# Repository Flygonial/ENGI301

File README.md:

<h1>ENGI301</h1>
Repository for ENGI301 course work

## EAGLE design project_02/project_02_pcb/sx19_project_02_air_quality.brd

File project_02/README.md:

This is the implementation for assignment project_02 in the course ENGI 301 at Rice University.

Included are the schematics, layout, and library in Autodesk EAGLE, along with basic manufacturing (gerber) files, a BOM, screenshots and PDFs that additionall document the design.

The board exists with the express purpose to implement the circuit in project_01 that joined all the PocketBeagle, PMS5003, CCS811, AHT10, and ILI9341 LCD together to form a more
elegant air quality module. Further work may entail design of a relatively rudimentary 3D printed case that utilizes the mounting holes on the PCB design, and this would likely still
run off USB power for packaging concerns.

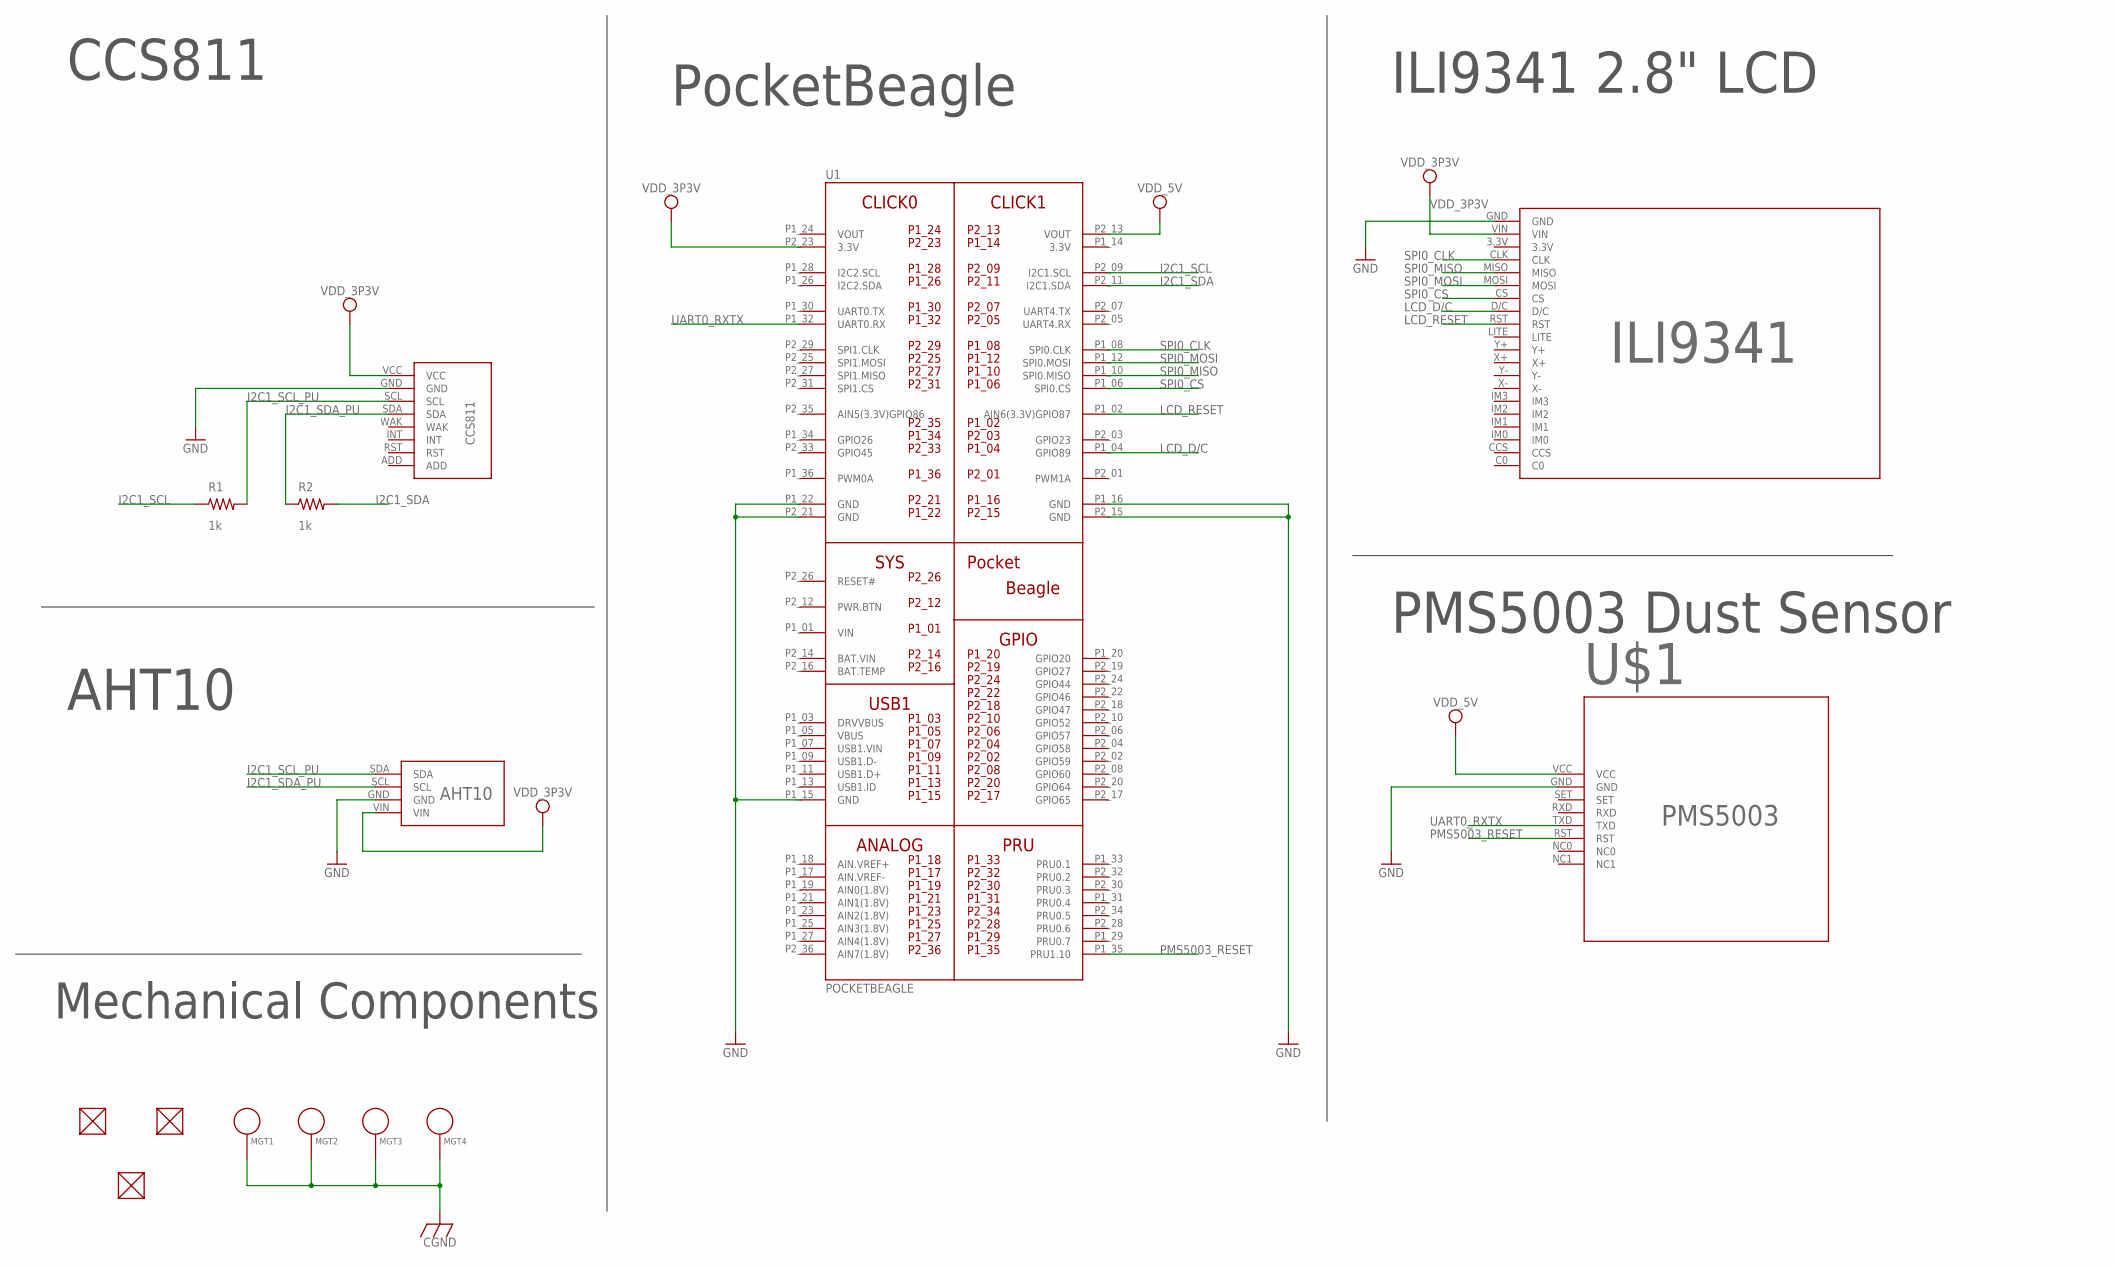
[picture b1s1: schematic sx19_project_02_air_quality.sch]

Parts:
B1: AHT10
B2: CCS811
B3: ILI9341
FUD1, FUD2, FUD3: FIDUCIAL; FIDUCIAL_40MIL
MGT1, MGT2, MGT3, MGT4: MOUNTING_HOLE
R1, R2: 1k; R0603
U1: POCKETBEAGLE
U$1: PMS5003

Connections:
3.3V: U1.P1_14 (3.3V)
BAT.VIN: U1.P2_14 (BAT.VIN)
CGND: MGT1.P$1, MGT2.P$1, MGT3.P$1, MGT4.P$1
GND: B1.GND, B2.GND, B3.GND, U1.P1_15 (GND), U1.P1_16 (GND), U1.P1_22 (GND), U1.P2_15 (GND), U1.P2_21 (GND), U$1.GND
I2C1_SCL: R1.1, U1.P2_09 (I2C1.SCL)
I2C1_SCL_PU: B1.SDA, B2.SCL, R1.2
I2C1_SDA: R2.2, U1.P2_11 (I2C1.SDA)
I2C1_SDA_PU: B1.SCL, B2.SDA, R2.1
LCD_D/C: B3.D/C, U1.P1_04 (GPIO89)
LCD_RESET: B3.RST, U1.P1_02 (AIN6(3.3V)GPIO87)
PMS5003_RESET: U1.P1_35 (PRU1.10), U$1.RST
SPI0_CLK: B3.CLK, U1.P1_08 (SPI0.CLK)
SPI0_CS: B3.CS, U1.P1_06 (SPI0.CS)
SPI0_MISO: B3.MISO, U1.P1_10 (SPI0.MISO)
SPI0_MOSI: B3.MOSI, U1.P1_12 (SPI0.MOSI)
UART0_RXTX: U1.P1_32 (UART0.RX), U$1.TXD
VDD_3P3V: B1.VIN, B2.VCC, B3.VIN, U1.P2_23 (3.3V)
VDD_5V: U1.P2_13 (VOUT), U$1.VCC
VIN: U1.P1_01 (VIN)
VOUT: U1.P1_24 (VOUT)

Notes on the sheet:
PocketBeagle
CCS811
AHT10
ILI9341 2.8" LCD
PMS5003 Dust Sensor
Mechanical Components

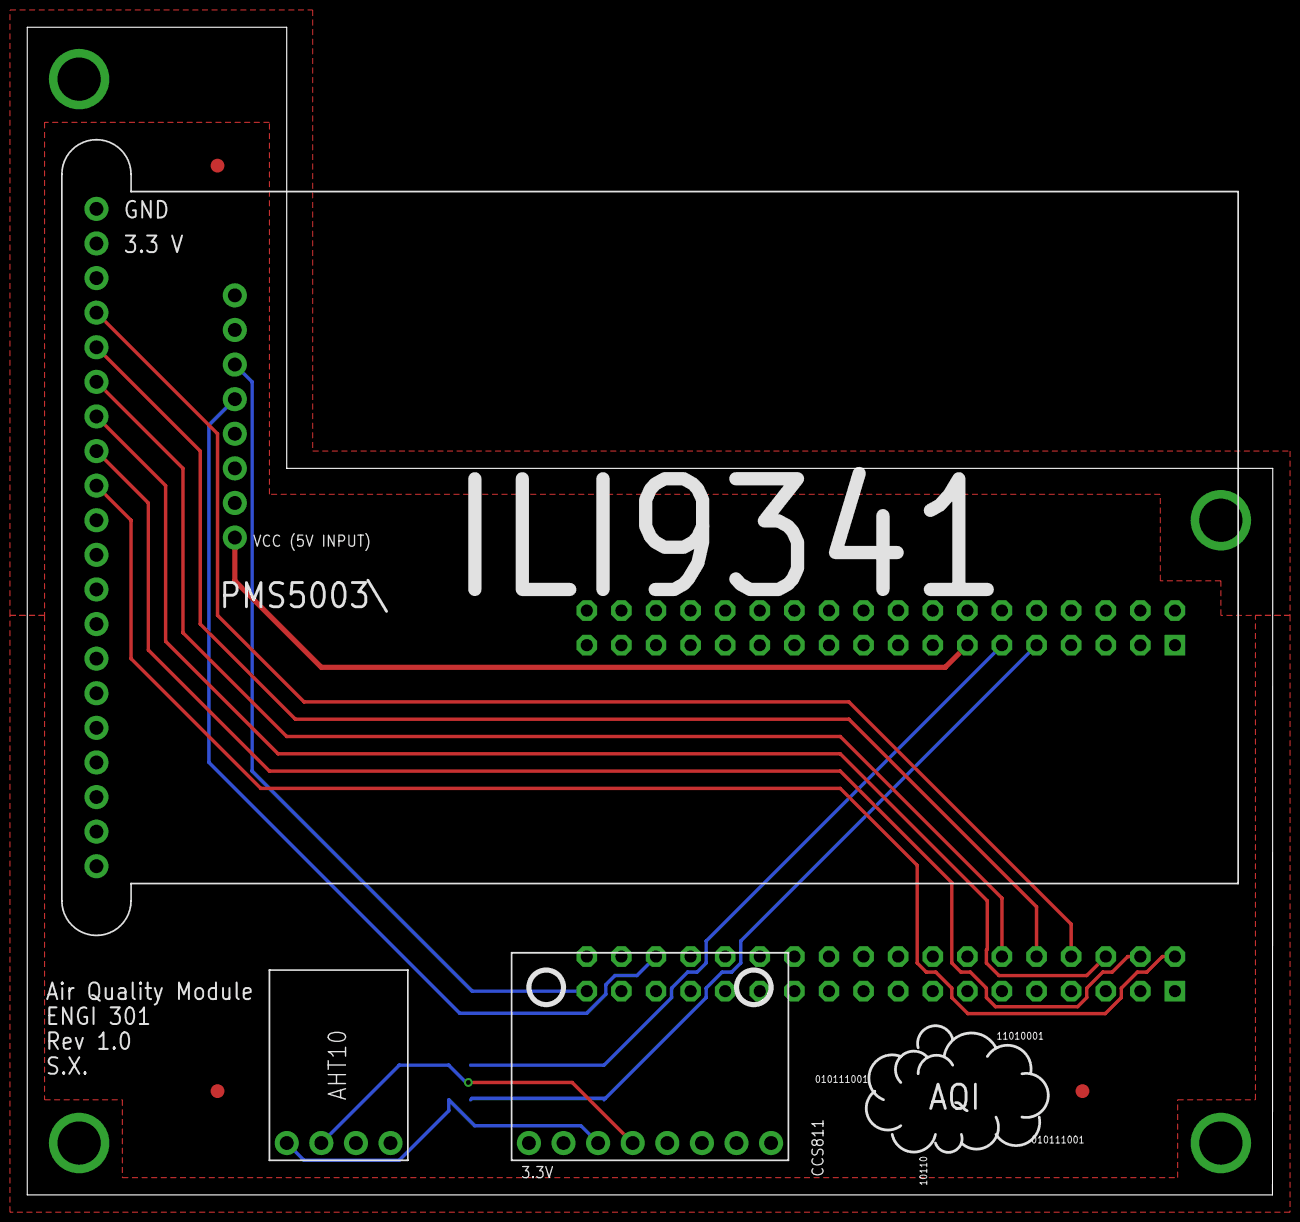
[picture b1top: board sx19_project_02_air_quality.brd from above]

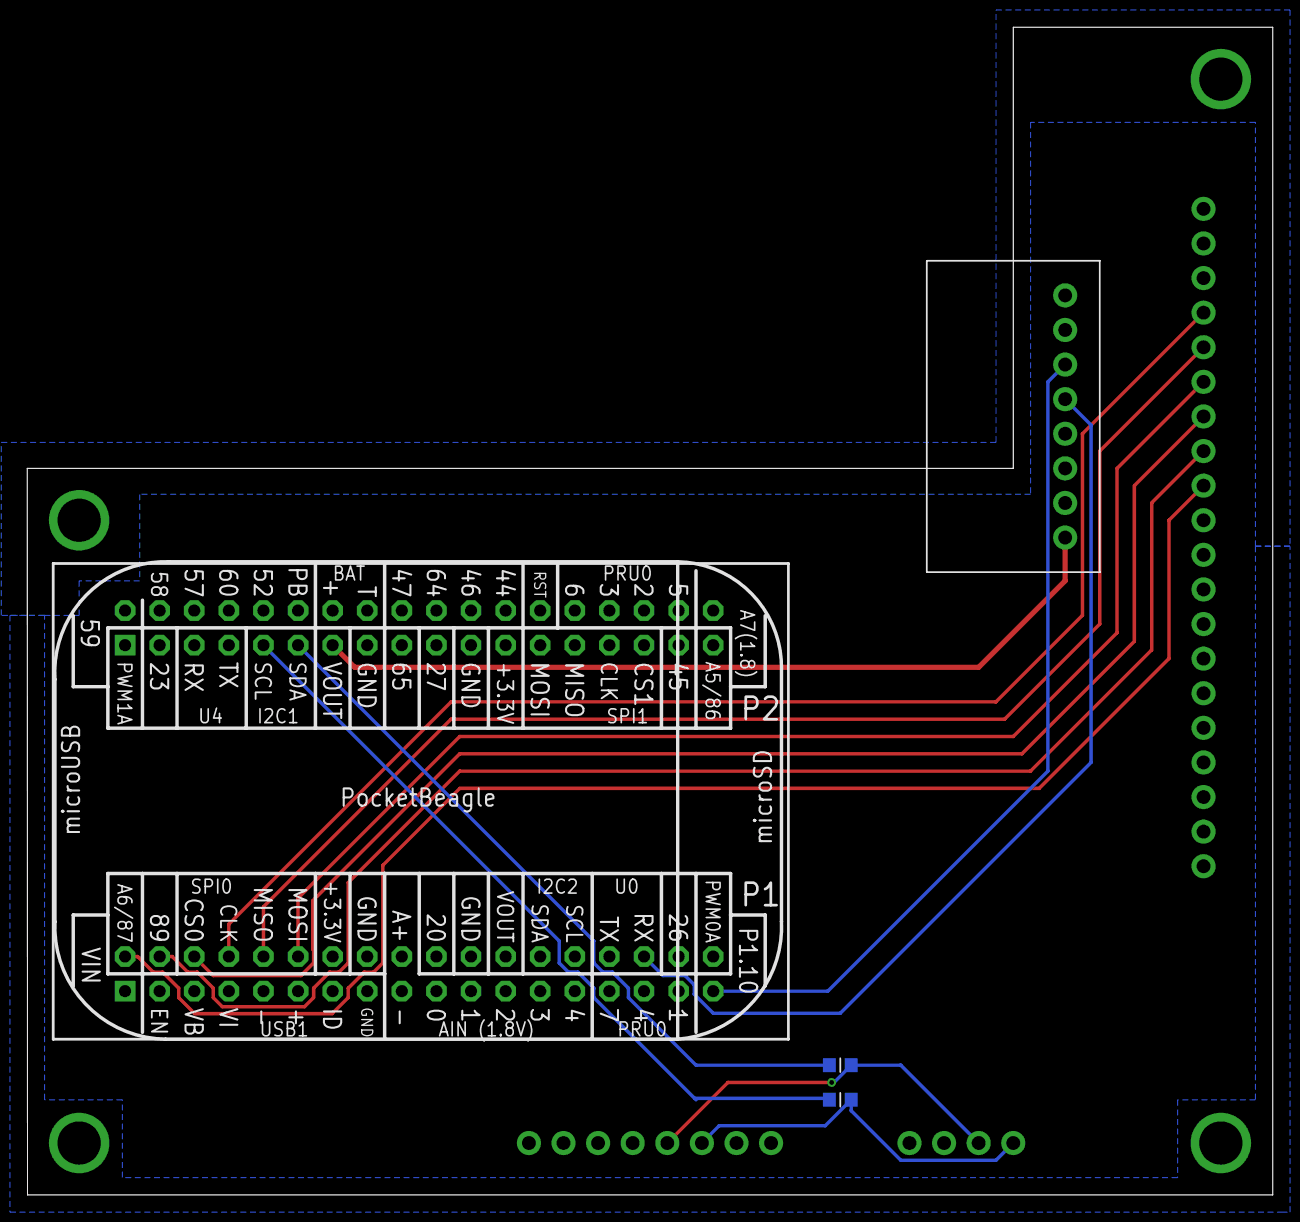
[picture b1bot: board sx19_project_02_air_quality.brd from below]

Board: 4 copper layers, 91.4 x 85.7 mm, 14 parts (4 on the bottom side), 16 nets.

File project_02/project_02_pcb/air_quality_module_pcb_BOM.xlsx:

Part | MPN / Manufacturer | Quantity | Description
B1 | AHT10 | 1 | Breakout board for the AHT10 integrated temperature and humidity sensor by Aoso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
B2 | CCS811 | 1 | CCS811 based a specific layout sold on Amazon. May be discontinued in favor of 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
B3 | ILI9341 | 1 | ILI9341 LCD based on the 2.8" Adafruit product
CGND | Generic | 2 | Copper ground layer as defined in layout
FUDx40 | Generic | 3 | 40 MIL fiducial
MGTx105 | Generic | 4 | 105 MIL Chassis Mounting Hole w/GND connection ability
R1 | Generic | 2 | R0603 1k ohm resistor
B4 | PMS5003 | 1 | Breakout board of the PMS5003 by Plantower and distributed by Adafruit. Connect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
B5 | POCKETBEAGLE-SC-569 | 1 | OSD3358 PocketBeagle series ARM® Cortex®-A8 MPU Embedded Evaluation Board

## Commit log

2021-10-07 Assignment 4 (Q1, Q2 Uploads)
    Added files and directories for simple_calc and blink_USR3.
2021-10-14 Uploading revised project proposal 1
    Updates components (changed screen, dust sensor), added story details in depth into presenter notes, and block diagrams.
2021-11-03 Concurrency Update with Cloud9 Workspace
    Project files as of 11/2/2021 10:15 PM
2021-11-08 Concurrency Update with Cloud9 Workspace
    Upated as of 11/8/21 at 1:54 PM
2021-11-09 Uploaded Project 1 Implementation Files
    All implementation files for Project 1 submission as of 8:27 PM, 11/8/21.
2021-11-09 Reuploading Project 1 within Python directory
    Submission for project_01 for ENGI 301 at Rice University
2021-11-09 Created README for project_01
2021-11-17 Uploading Project 02 Proposal
    Initial draft of project proposal with included paths and directories as specified
2021-12-15 Project 02 Top & Bottom Layout Screenshots
    Added for phase two of the project, screenshots of the board design for the top and bottom layer of the board (with additional details included).
2021-12-15 Project 02 Implementation Files
    A collection of the schematics, layout, library, BOM, and manufacturing files for project_02
2021-12-15 Project 02 README
